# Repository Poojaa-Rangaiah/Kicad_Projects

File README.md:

# Kicad Projects
Welcome to my Kicad Projects!<br>
* This repository contains the Kicad PCB files from which I learnt to build the PCB schematic and layout from a [Udemy course](https://www.udemy.com/course/kicad-like-a-pro-3e/?couponCode=ACCAGE0923).

## 4 Layer MCU Datalogger PCB

## 2 layer MCU Datalogger PCB

## POWER SUPPLY PCB

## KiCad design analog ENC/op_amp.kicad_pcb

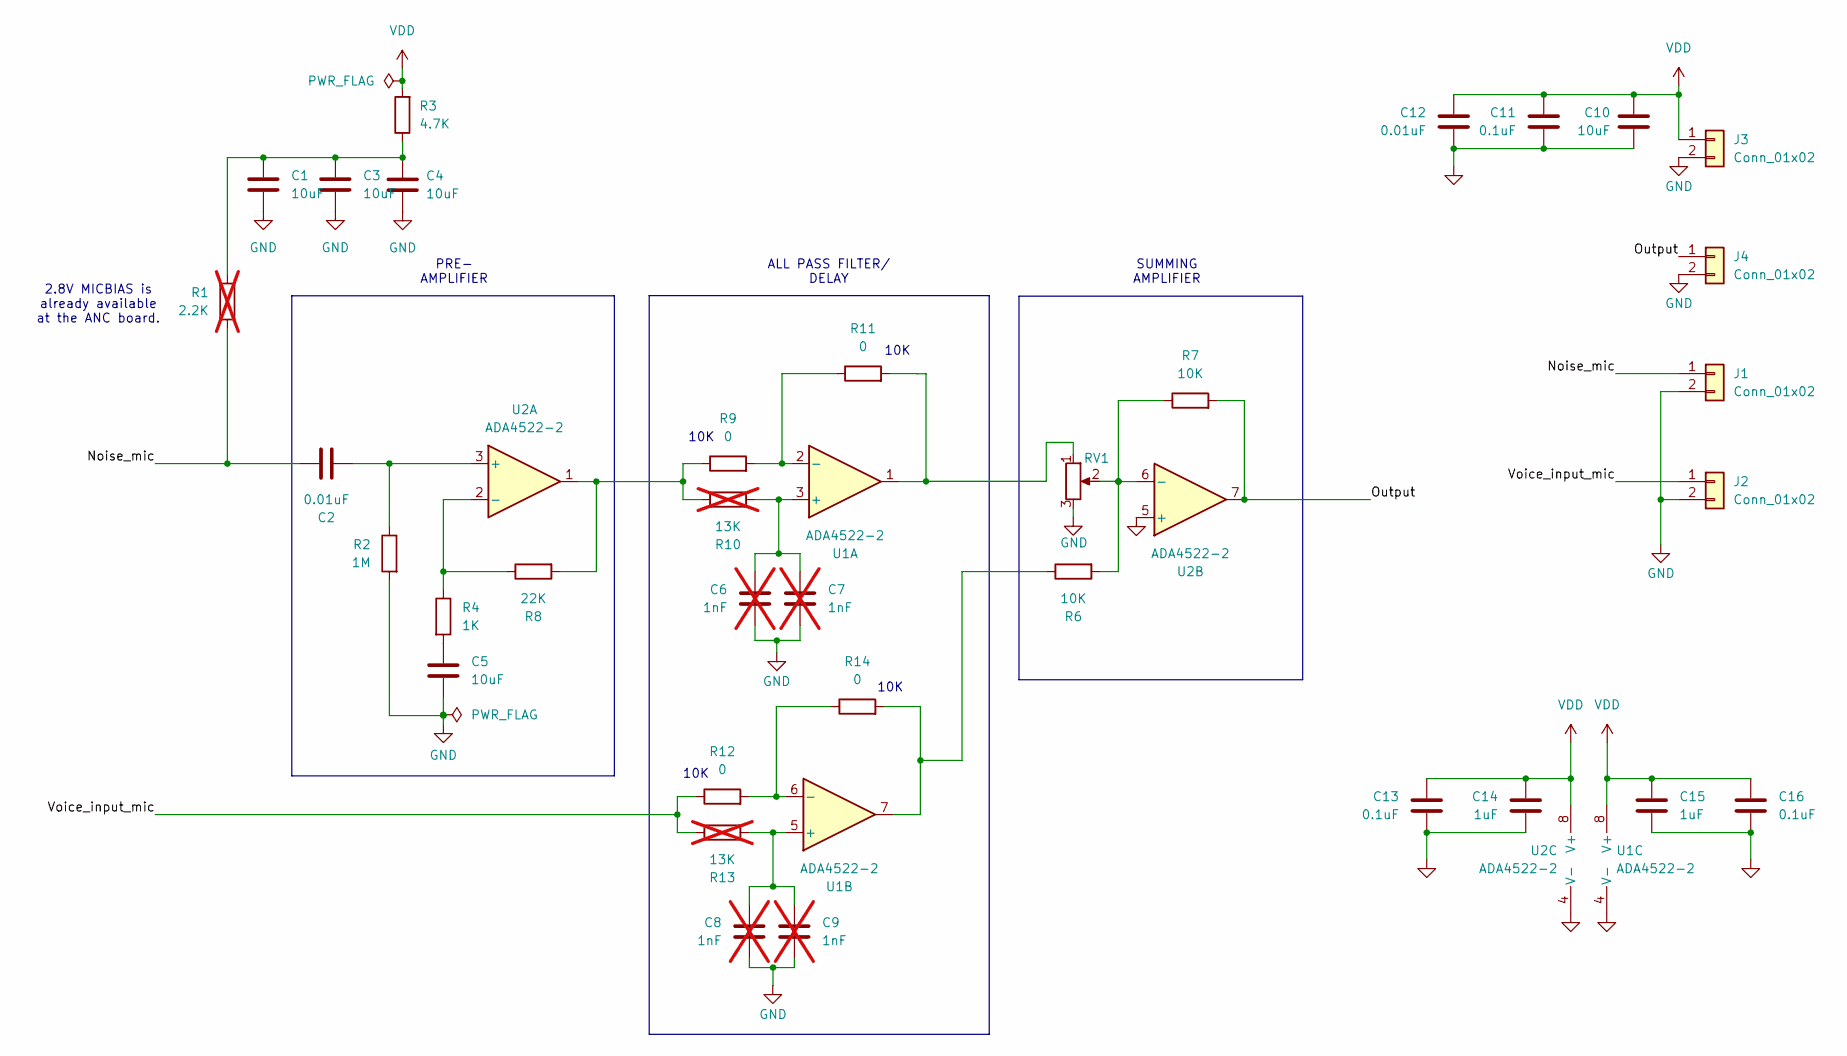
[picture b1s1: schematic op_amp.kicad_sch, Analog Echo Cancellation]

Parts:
C1, C3, C4, C5, C10: 10uF; C_0402_1005Metric_Pad0.74x0.62mm_HandSolder
C2, C12: 0.01uF; C_0402_1005Metric_Pad0.74x0.62mm_HandSolder
C6, C7, C8, C9: 1nF; C_0402_1005Metric_Pad0.74x0.62mm_HandSolder; not fitted
C11, C13, C16: 0.1uF; C_0402_1005Metric_Pad0.74x0.62mm_HandSolder
C14, C15: 1uF; C_0402_1005Metric_Pad0.74x0.62mm_HandSolder
J1, J2, J3, J4: Conn_01x02; PinHeader_2x01_P2.54mm_Vertical
R1: 2.2K; R_0402_1005Metric_Pad0.72x0.64mm_HandSolder; not fitted
R2: 1M; R_0402_1005Metric_Pad0.72x0.64mm_HandSolder
R3: 4.7K; R_0402_1005Metric_Pad0.72x0.64mm_HandSolder
R4: 1K; R_0402_1005Metric_Pad0.72x0.64mm_HandSolder
R6, R7: 10K; R_0402_1005Metric_Pad0.72x0.64mm_HandSolder
R8: 22K; R_0402_1005Metric_Pad0.72x0.64mm_HandSolder
R9, R11, R12, R14: 0; R_0402_1005Metric_Pad0.72x0.64mm_HandSolder
R10, R13: 13K; R_0402_1005Metric_Pad0.72x0.64mm_HandSolder; not fitted
RV1: R_Potentiometer; Potentiometer_Runtron_RM-065_Vertical
U1, U2: ADA4522-2; SOP65P490X110-8N

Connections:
/Noise_mic: C2.1, J1.1, R1.2
/Output: J4.1, R7.2, U2.7
/Voice_input_mic: J2.1, R12.1, R13.1
GND: C1.2, C3.2, C4.2, C5.2, C6.2, C7.2, C8.2, C9.2, C10.2, C11.2, C12.2, C13.2, C14.2, C15.2, C16.2, J1.2, J2.2, J3.2, J4.2, R2.2, RV1.3, U1.4 (V-), U2.4 (V-), U2.5 (+)
unnamed: C1.1, C3.1, C4.1, R1.1, R3.1
unnamed: C5.1, R4.2
unnamed: R8.2, R9.1, R10.1, U2.1
unnamed: R11.2, RV1.1, U1.1
unnamed: R6.1, R14.2, U1.7
unnamed: C6.1, C7.1, R10.2, U1.3 (+)
unnamed: R9.2, R11.1, U1.2 (-)
unnamed: C8.1, C9.1, R13.2, U1.5 (+)
unnamed: R12.2, R14.1, U1.6 (-)
unnamed: C2.2, R2.1, U2.3 (+)
unnamed: R4.1, R8.1, U2.2 (-)
unnamed: R6.2, R7.1, RV1.2, U2.6 (-)
VDD: C10.1, C11.1, C12.1, C13.1, C14.1, C15.1, C16.1, J3.1, R3.2, U1.8 (V+), U2.8 (V+)

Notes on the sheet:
PRE- AMPLIFIER
10K
ALL PASS FILTER/ DELAY
2.8V MICBIAS is already available at the ANC board.
SUMMING AMPLIFIER

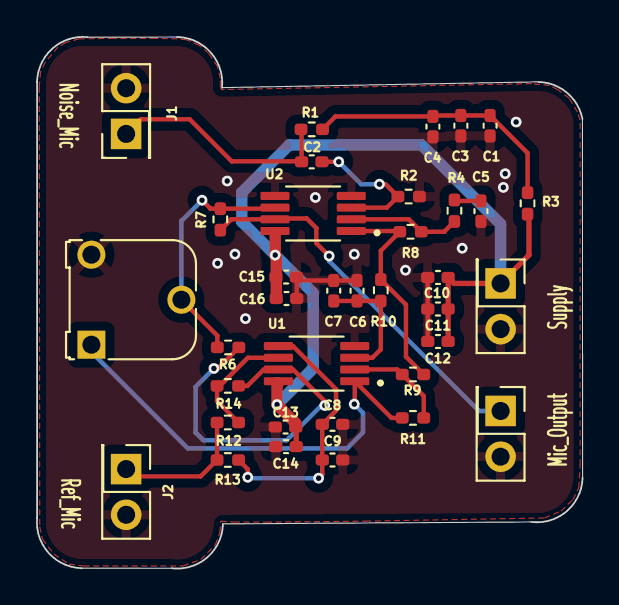
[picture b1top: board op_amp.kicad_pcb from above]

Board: 2 copper layers, 30.3 x 29.5 mm, 36 parts (0 on the bottom side), 17 nets.

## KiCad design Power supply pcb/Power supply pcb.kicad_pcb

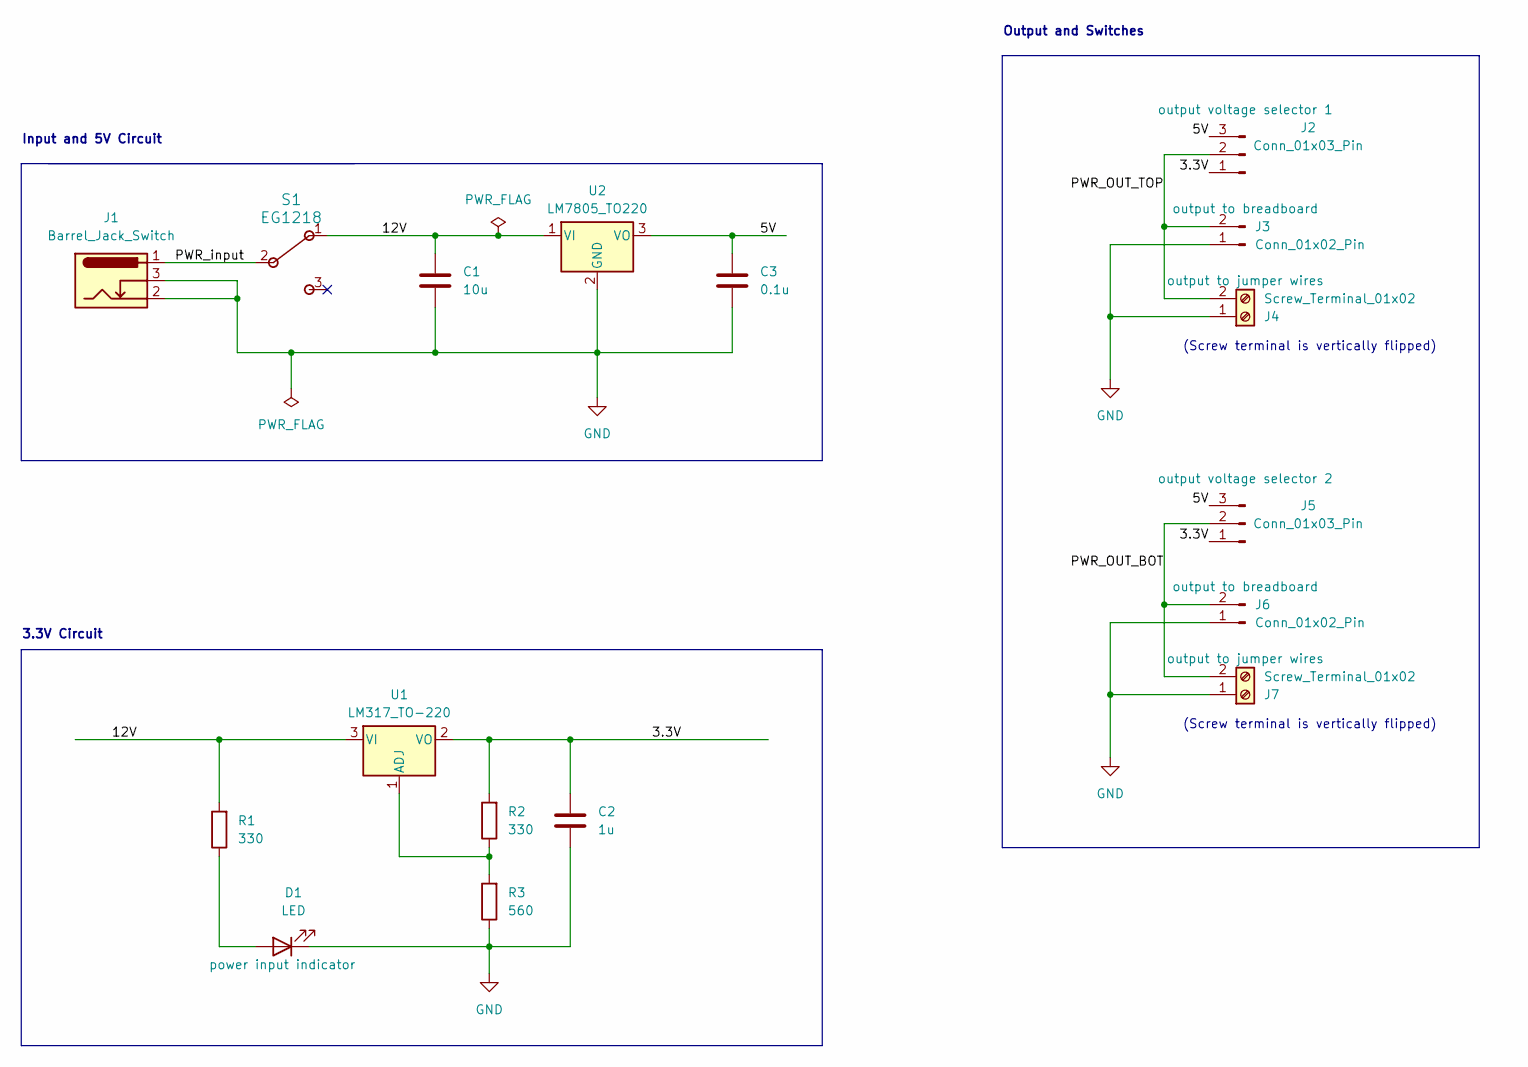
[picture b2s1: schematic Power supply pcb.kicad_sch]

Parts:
C1: 10u; C_Disc_D3.0mm_W1.6mm_P2.50mm
C2: 1u; C_Disc_D3.0mm_W1.6mm_P2.50mm
C3: 0.1u; C_Disc_D3.0mm_W1.6mm_P2.50mm
D1: LED; LED_D5.0mm
J1: Barrel_Jack_Switch; BarrelJack_Horizontal
J2, J5: Conn_01x03_Pin; PinHeader_1x03_P2.54mm_Vertical
J3, J6: Conn_01x02_Pin; PinHeader_1x02_P2.54mm_Vertical
J4, J7: Screw_Terminal_01x02; TerminalBlock_bornier-2_P5.08mm
R1, R2: 330; R_Axial_DIN0204_L3.6mm_D1.6mm_P7.62mm_Horizontal
R3: 560; R_Axial_DIN0204_L3.6mm_D1.6mm_P7.62mm_Horizontal
S1: EG1218; SW_1218_EWI
U1: LM317_TO-220; TO-220-3_Vertical
U2: LM7805_TO220; TO-220-3_Vertical

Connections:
/3.3V: C2.1, J2.1, J5.1, R2.2, U1.2 (VO)
/5V: C3.1, J2.3, J5.3, U2.3 (VO)
/12V: C1.1, R1.2, S1.1, U1.3 (VI), U2.1 (VI)
/PWR_OUT_BOT: J5.2, J6.2, J7.2
/PWR_OUT_TOP: J2.2, J3.2, J4.2
/PWR_input: J1.1, S1.2
GND: C1.2, C2.2, C3.2, D1.1 (K), J1.2, J1.3, J3.1, J4.1, J6.1, J7.1, R3.1, U2.2 (GND)
unnamed: D1.2 (A), R1.1
unnamed: R2.1, R3.2, U1.1 (ADJ)

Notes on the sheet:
3.3V Circuit
(Screw terminal is vertically flipped)
Output and Switches
Input and 5V Circuit

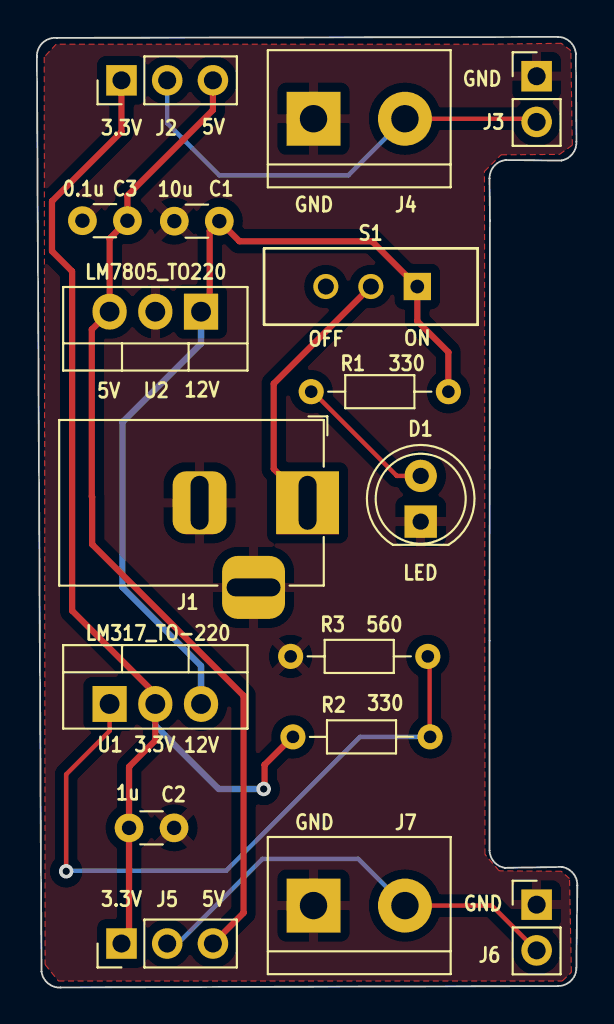
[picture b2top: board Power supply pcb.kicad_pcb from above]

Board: 2 copper layers, 30.0 x 52.8 mm, 17 parts (0 on the bottom side), 9 nets.

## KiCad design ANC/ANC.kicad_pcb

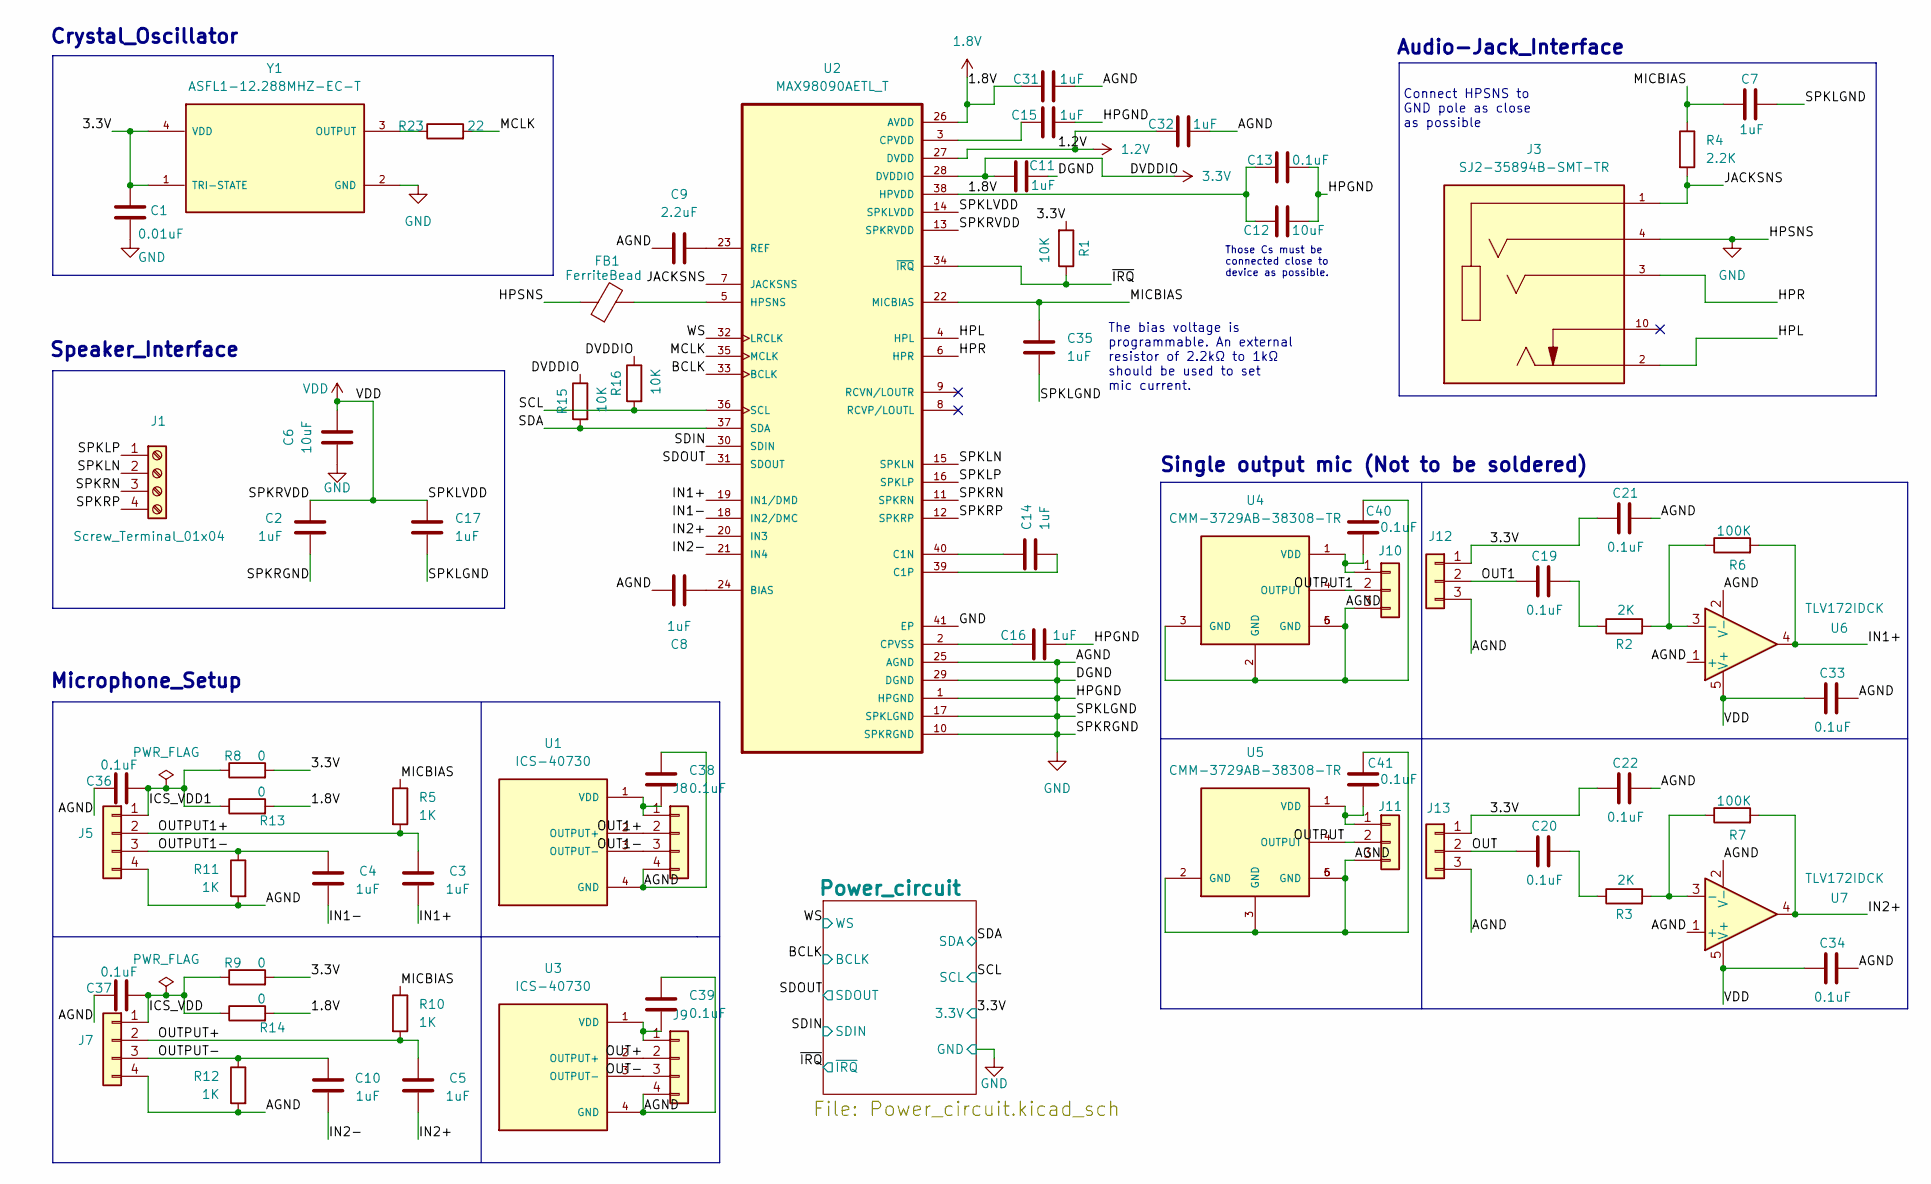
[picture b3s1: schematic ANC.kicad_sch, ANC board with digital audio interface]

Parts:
C1: 0.01uF; C_0402_1005Metric_Pad0.74x0.62mm_HandSolder
C2, C3, C4, C5, C7, C8, C10, C11, C14, C15, C16, C17, C31, C32, C35: 1uF; C_0402_1005Metric_Pad0.74x0.62mm_HandSolder
C6, C12: 10uF; C_0805_2012Metric_Pad1.18x1.45mm_HandSolder
C9: 2.2uF; C_0805_2012Metric_Pad1.18x1.45mm_HandSolder
C13, C19, C20, C21, C22, C33, C34, C36, C37, C38, C39, C40, C41: 0.1uF; C_0402_1005Metric_Pad0.74x0.62mm_HandSolder
FB1: FerriteBead; L_0402_1005Metric
J1: Screw_Terminal_01x04; TE_282836-4
J3: SJ2-35894B-SMT-TR; CUI_SJ2-35894B-SMT-TR; PARTREV 1.04
J5, J7, J8, J9: Conn_01x04; PinSocket_1x04_P2.54mm_Vertical
J10, J11, J12, J13: Conn_01x03; PinSocket_1x03_P2.54mm_Vertical
R1, R15, R16: 10K; R_0402_1005Metric_Pad0.72x0.64mm_HandSolder
R2, R3: 2K; R_0402_1005Metric_Pad0.72x0.64mm_HandSolder
R4: 2.2K; R_0402_1005Metric_Pad0.72x0.64mm_HandSolder
R5, R10, R11, R12: 1K; R_0402_1005Metric_Pad0.72x0.64mm_HandSolder
R6, R7: 100K; R_0402_1005Metric_Pad0.72x0.64mm_HandSolder
R8, R9, R13, R14: 0; R_0402_1005Metric_Pad0.72x0.64mm_HandSolder
R23: 22; R_0402_1005Metric_Pad0.72x0.64mm_HandSolder
U1, U3: ICS-40730; MIC_ICS-40730
U2: MAX98090AETL_T; QFN40P500X500X80-41N
U4, U5: CMM-3729AB-38308-TR; XDCR_CMM-3729AB-38308-TR
U6, U7: TLV172IDCK; SOT-353_SC-70-5
Y1: ASFL1-12.288MHZ-EC-T; XTAL_ASFL1-12.288MHZ-EC-T; PARTREV 04.13.11

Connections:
1.2V: C32.2, U2.27 (DVDD); also elsewhere on the board
1.8V: C12.2, C13.2, C31.2, R13.2, R14.2, U2.26 (AVDD), U2.38 (HPVDD); also elsewhere on the board
3.3V: C1.1, C11.2, C21.2, C22.2, J12.1, J13.1, R1.2, R8.2, R9.2, R15.1, R16.1, U2.28 (DVDDIO), Y1.1 (TRI-STATE), Y1.4 (VDD); also elsewhere on the board
/BCLK: U2.33 (BCLK); also elsewhere on the board
/HPL: J3.2, U2.4 (HPL)
/HPR: J3.3, U2.6 (HPR)
/ICS_VDD: C37.1, J7.1, R9.1, R14.1
/ICS_VDD1: C36.1, J5.1, R8.1, R13.1
/IN1+: C3.1, R6.2, U2.19 (IN1/DMD), U6.4
/IN1-: C4.2, U2.18 (IN2/DMC)
/IN2+: C5.1, R7.2, U2.20 (IN3), U7.4
/IN2-: C10.2, U2.21 (IN4)
/JACKSNS: J3.1, R4.2, U2.7 (JACKSNS)
/MCLK: R23.2, U2.35 (MCLK)
/MICBIAS: C7.1, C35.1, R4.1, R5.1, R10.1, U2.22 (MICBIAS)
/OUT: C20.2, J13.2
/OUT1: C19.2, J12.2
/OUT1+: J8.2, U1.2 (OUTPUT+)
/OUT1-: J8.3, U1.3 (OUTPUT-)
/OUT+: J9.2, U3.2 (OUTPUT+)
/OUT-: J9.3, U3.3 (OUTPUT-)
/OUTPUT: J11.2, U5.4 (OUTPUT)
/OUTPUT1: J10.2, U4.4 (OUTPUT)
/OUTPUT1+: C3.2, J5.2, R5.2
/OUTPUT1-: C4.1, J5.3, R11.1
/OUTPUT+: C5.2, J7.2, R10.2
/OUTPUT-: C10.1, J7.3, R12.1
/SCL: R16.2, U2.36 (SCL); also elsewhere on the board
/SDA: R15.2, U2.37 (SDA); also elsewhere on the board
/SDIN: U2.30 (SDIN); also elsewhere on the board
/SDOUT: U2.31 (SDOUT); also elsewhere on the board
/SPKLN: J1.2, U2.15 (SPKLN)
/SPKLP: J1.1, U2.16 (SPKLP)
/SPKRN: J1.3, U2.11 (SPKRN)
/SPKRP: J1.4, U2.12 (SPKRP)
/WS: U2.32 (LRCLK); also elsewhere on the board
/~IRQ: R1.1, U2.34 (~IRQ); also elsewhere on the board
GND: C1.2, C2.2, C6.1, C7.2, C8.2, C9.2, C11.1, C12.1, C13.1, C15.1, C16.1, C17.2, C21.1, C22.1, C31.1, C32.1, C33.1, C34.1, C35.2, C36.2, C37.2, C38.1, C39.1, C40.1, C41.1, FB1.1, J3.4, J5.4, J7.4, J8.4, J9.4, J10.3, J11.3, J12.3, J13.3, R11.2, R12.2, U1.4 (GND), U2.1 (HPGND), U2.10 (SPKRGND), U2.17 (SPKLGND), U2.25 (AGND), U2.29 (DGND), U2.41 (EP), U3.4 (GND), U4.2 (GND), U4.3 (GND), U4.5 (GND), U4.6 (GND), U5.2 (GND), U5.3 (GND), U5.5 (GND), U5.6 (GND), U6.1 (+), U6.2 (V-), U7.1 (+), U7.2 (V-), Y1.2 (GND); also elsewhere on the board
unnamed: C19.1, R2.1
unnamed: C20.1, R3.1
unnamed: C38.2, J8.1, U1.1 (VDD)
unnamed: C39.2, J9.1, U3.1 (VDD)
unnamed: C40.2, J10.1, U4.1 (VDD)
unnamed: C41.2, J11.1, U5.1 (VDD)
unnamed: C8.1, U2.24 (BIAS)
unnamed: C14.2, U2.40 (C1N)
unnamed: C14.1, U2.39 (C1P)
unnamed: C15.2, U2.3 (CPVDD)
unnamed: C16.2, U2.2 (CPVSS)
unnamed: FB1.2, U2.5 (HPSNS)
unnamed: C9.1, U2.23 (REF)
unnamed: R2.2, R6.1, U6.3 (-)
unnamed: R3.2, R7.1, U7.3 (-)
unnamed: R23.1, Y1.3 (OUTPUT)
VDD: C2.1, C6.2, C17.1, C33.2, C34.2, U2.13 (SPKRVDD), U2.14 (SPKLVDD), U6.5 (V+), U7.5 (V+); also elsewhere on the board

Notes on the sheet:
Microphone_Setup
Single output mic (Not to be soldered)
The bias voltage is programmable. An external resistor of 2.2kΩ to 1kΩ should be used to set mic current.
Connect HPSNS to GND pole as close as possible
Those Cs must be connected close to device as possible.
Audio-Jack_Interface
Crystal_Oscillator
Speaker_Interface

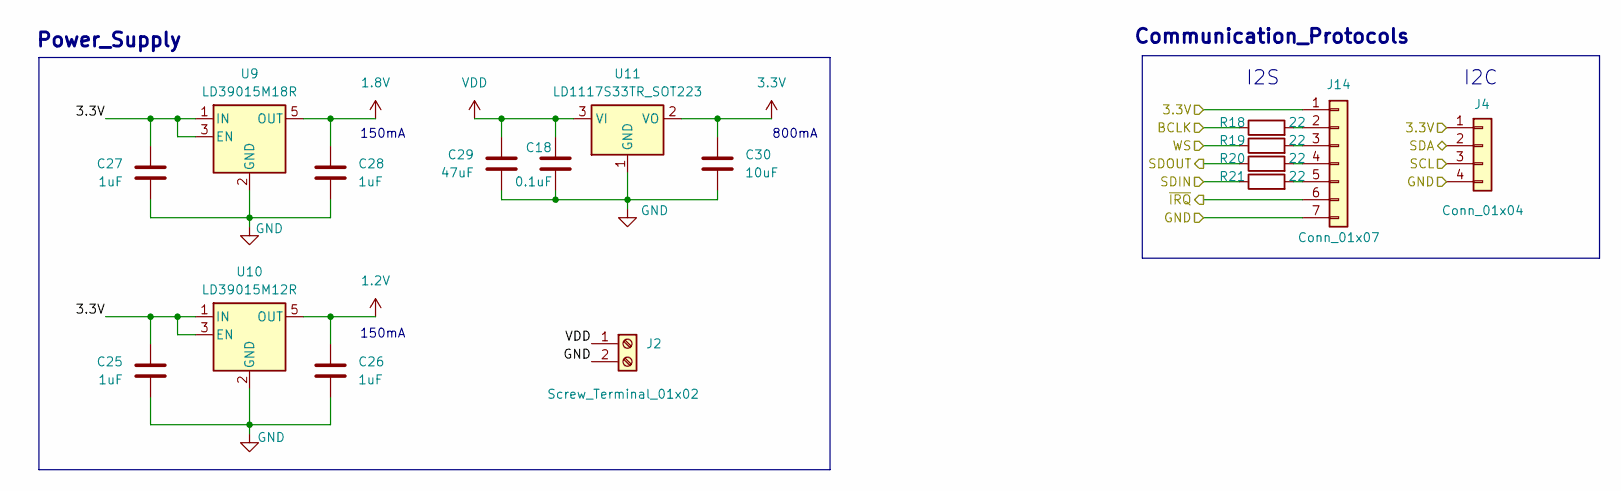
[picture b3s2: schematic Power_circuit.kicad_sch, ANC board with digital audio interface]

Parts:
C18: 0.1uF; C_0402_1005Metric_Pad0.74x0.62mm_HandSolder
C25, C26, C27, C28: 1uF; C_0402_1005Metric_Pad0.74x0.62mm_HandSolder
C29: 47uF; C_0805_2012Metric_Pad1.18x1.45mm_HandSolder
C30: 10uF; C_0805_2012Metric_Pad1.18x1.45mm_HandSolder
J2: Screw_Terminal_01x02; TE_282836-2
J4: Conn_01x04; PinHeader_1x04_P2.54mm_Vertical
J14: Conn_01x07; PinHeader_1x07_P2.54mm_Vertical
R18, R19, R20, R21: 22; R_0402_1005Metric_Pad0.72x0.64mm_HandSolder
U9: LD39015M18R; SOT-23-5
U10: LD39015M12R; SOT-23-5
U11: LD1117S33TR_SOT223; SOT-223-3_TabPin2

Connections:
1.2V: C26.1, U10.5 (OUT); also elsewhere on the board
1.8V: C28.1, U9.5 (OUT); also elsewhere on the board
3.3V: C25.1, C27.1, C30.1, J4.1, J14.1, U9.1 (IN), U9.3 (EN), U10.1 (IN), U10.3 (EN), U11.2 (VO); also elsewhere on the board
/BCLK: R18.1; also elsewhere on the board
/SCL: J4.3; also elsewhere on the board
/SDA: J4.2; also elsewhere on the board
/SDIN: R21.1; also elsewhere on the board
/SDOUT: R20.1; also elsewhere on the board
/WS: R19.1; also elsewhere on the board
/~IRQ: J14.6; also elsewhere on the board
GND: C18.1, C25.2, C26.2, C27.2, C28.2, C29.2, C30.2, J2.2, J4.4, J14.7, U9.2 (GND), U10.2 (GND), U11.1 (GND); also elsewhere on the board
unnamed: J14.2, R18.2
unnamed: J14.3, R19.2
unnamed: J14.4, R20.2
unnamed: J14.5, R21.2
VDD: C18.2, C29.1, J2.1, U11.3 (VI); also elsewhere on the board

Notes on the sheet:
150mA
Communication_Protocols
I2S
I2C
800mA
Power_Supply

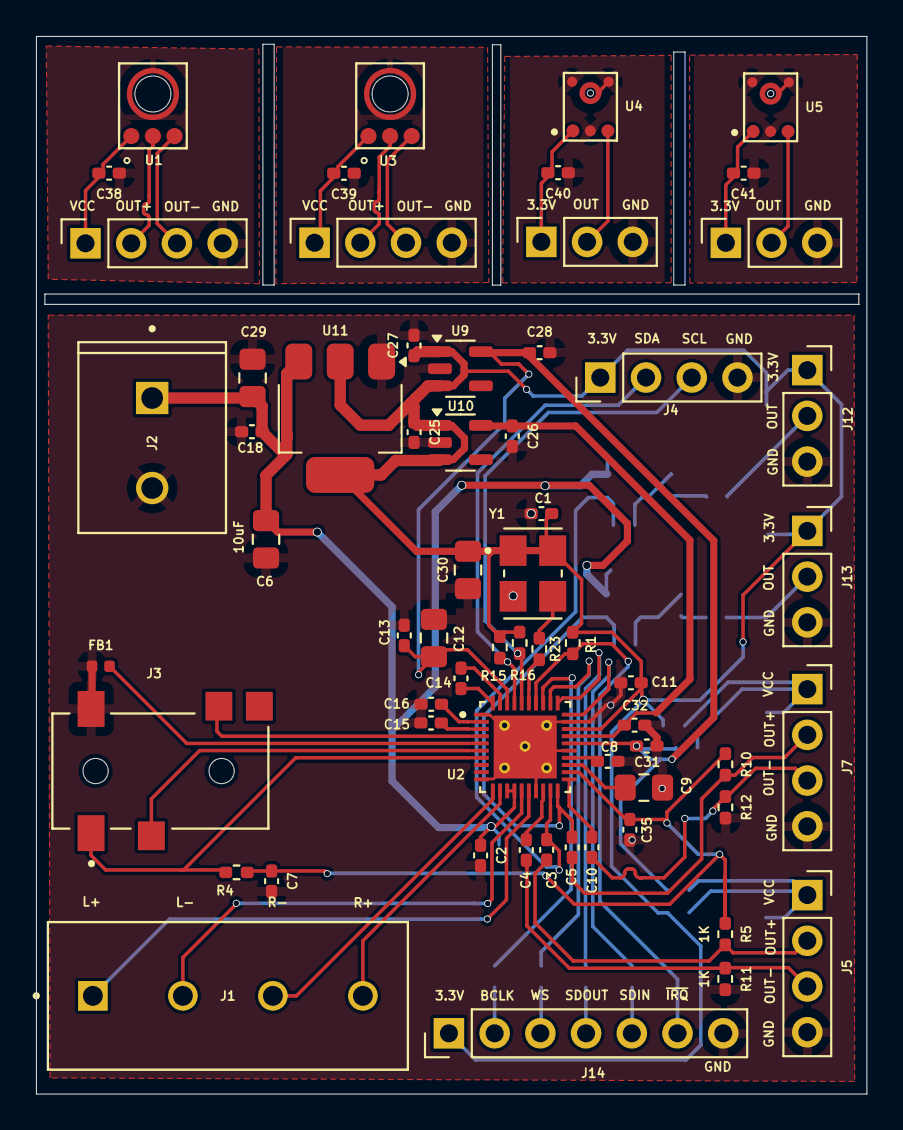
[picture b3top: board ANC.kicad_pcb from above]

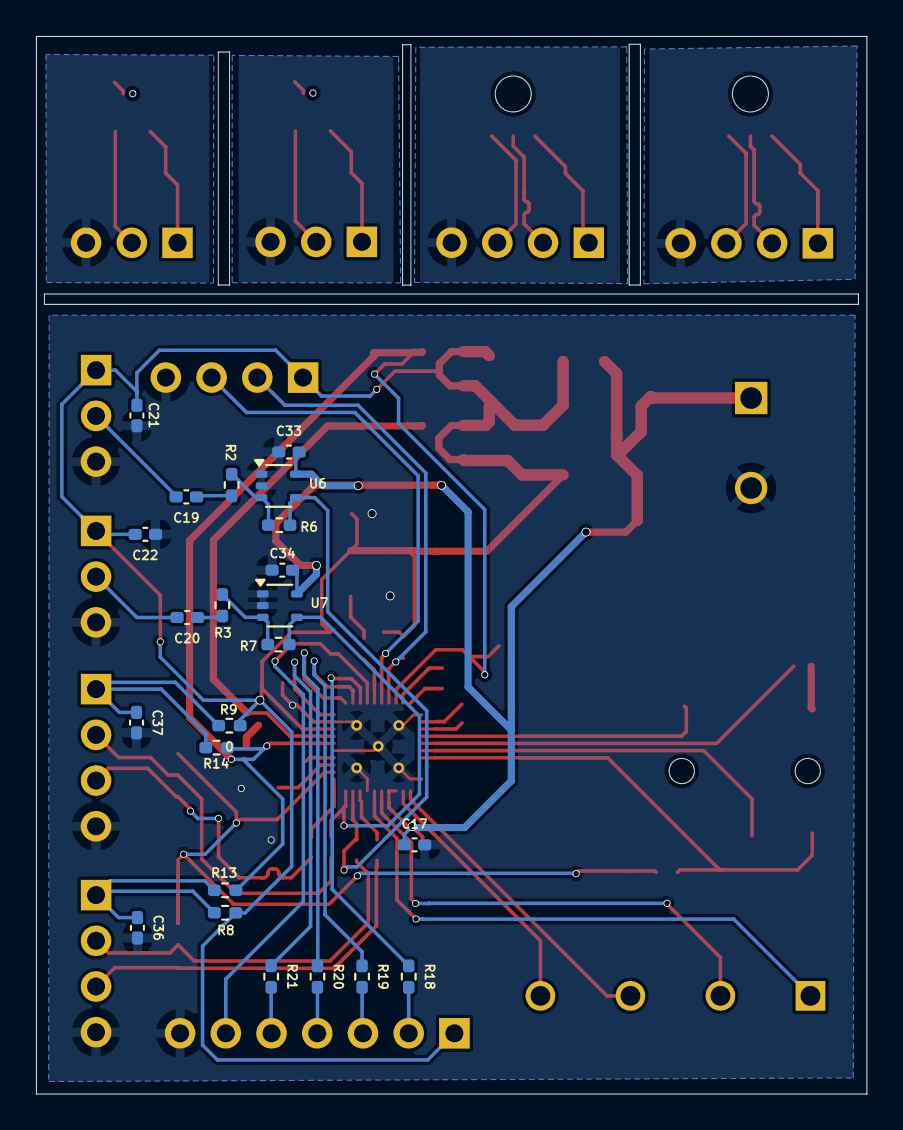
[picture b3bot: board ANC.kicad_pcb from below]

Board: 2 copper layers, 46.1 x 58.8 mm, 85 parts (23 on the bottom side), 59 nets.

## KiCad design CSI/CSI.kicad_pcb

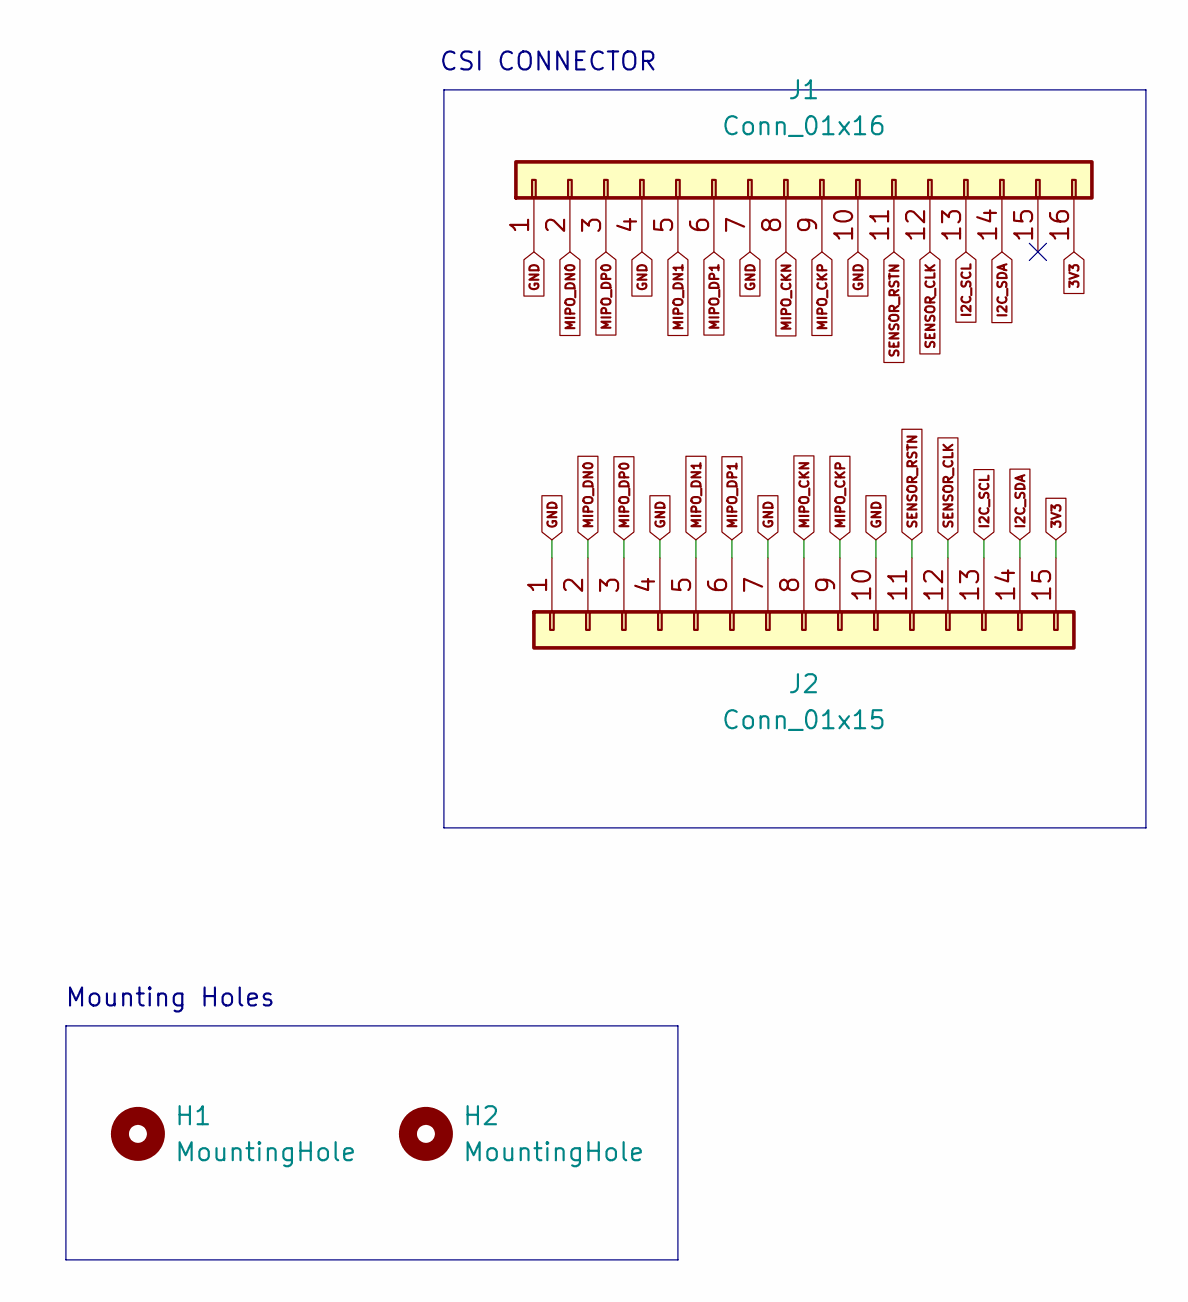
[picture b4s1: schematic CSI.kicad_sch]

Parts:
H1, H2: MountingHole; MountingHole_2.1mm
J1: Conn_01x16; CON_527461671_MOL
J2: Conn_01x15; TE_1-84952-5_1x15-1MP_P1.0mm_Horizontal

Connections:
3V3: J1.16, J2.15
GND: J1.1, J1.4, J1.7, J1.10, J2.1, J2.4, J2.7, J2.10
I2C_SCL: J1.13, J2.13
I2C_SDA: J1.14, J2.14
MIPO_CKN: J1.8, J2.8
MIPO_CKP: J1.9, J2.9
MIPO_DN0: J1.2, J2.2
MIPO_DN1: J1.5, J2.5
MIPO_DP0: J1.3, J2.3
MIPO_DP1: J1.6, J2.6
SENSOR_CLK: J1.12, J2.12
SENSOR_RSTN: J1.11, J2.11

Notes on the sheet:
Mounting Holes
CSI CONNECTOR

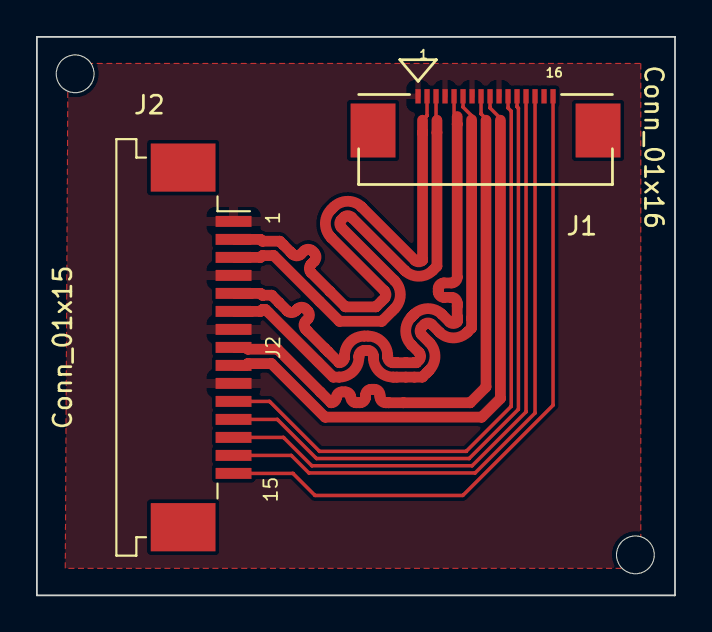
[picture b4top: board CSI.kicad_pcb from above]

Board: 2 copper layers, 35.5 x 31.0 mm, 4 parts (0 on the bottom side), 12 nets.

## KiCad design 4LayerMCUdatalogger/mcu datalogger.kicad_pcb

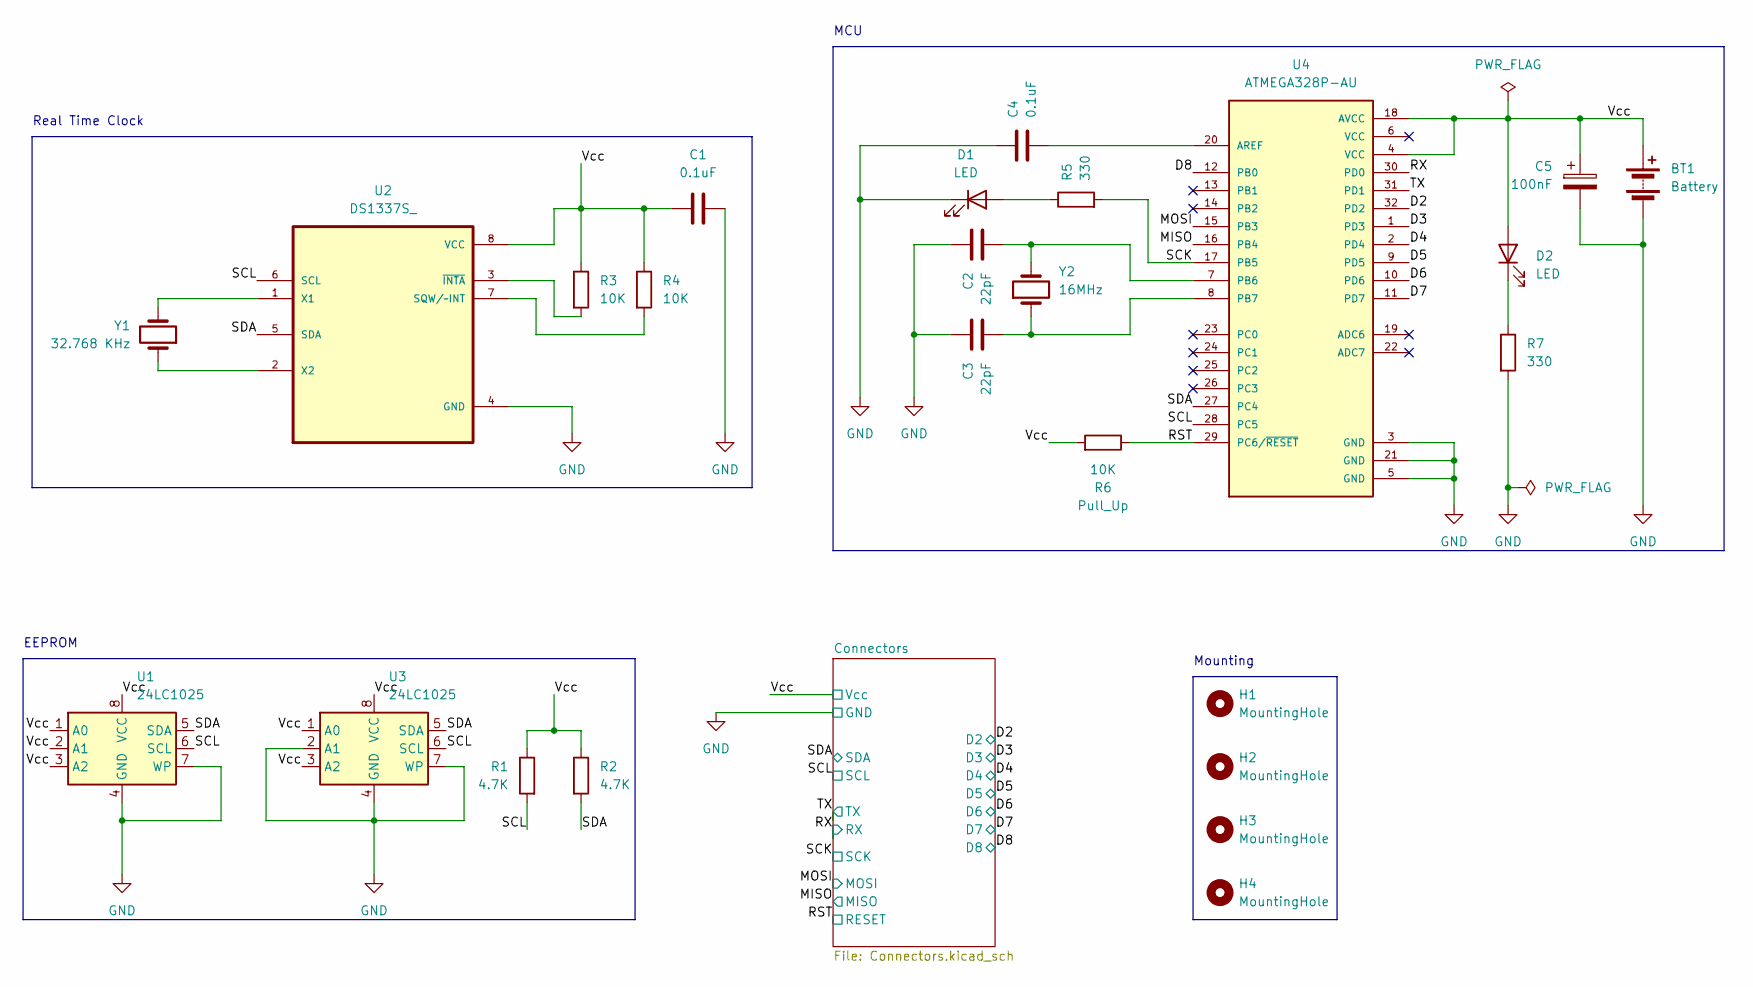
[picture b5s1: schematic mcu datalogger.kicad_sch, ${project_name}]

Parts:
BT1: Battery; PinHeader_1x02_P2.54mm_Vertical
C1, C4: 0.1uF; C_0805_2012Metric
C2, C3: 22pF; C_0805_2012Metric
C5: 100nF; C_0805_2012Metric
D1, D2: LED; LED_0805_2012Metric
H1, H2, H3, H4: MountingHole; MountingHole_2.1mm
R1, R2: 4.7K; R_0805_2012Metric
R3, R4, R6: 10K; R_0805_2012Metric
R5, R7: 330; R_0805_2012Metric
U1, U3: 24LC1025; SOIC-8_3.9x4.9mm_P1.27mm
U2: DS1337S_; SOIC127P600X175-8N
U4: ATMEGA328P-AU; QFP80P900X900X120-32N; PARTREV 8271A
Y1: 32.768 KHz; Crystal_SMD_5032-2Pin_5.0x3.2mm_HandSoldering
Y2: 16MHz; Crystal_SMD_5032-2Pin_5.0x3.2mm_HandSoldering

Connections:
/D2: U4.32 (PD2); also elsewhere on the board
/D3: U4.1 (PD3); also elsewhere on the board
/D4: U4.2 (PD4); also elsewhere on the board
/D5: U4.9 (PD5); also elsewhere on the board
/D6: U4.10 (PD6); also elsewhere on the board
/D7: U4.11 (PD7); also elsewhere on the board
/D8: U4.12 (PB0); also elsewhere on the board
/MISO: U4.16 (PB4); also elsewhere on the board
/MOSI: U4.15 (PB3); also elsewhere on the board
/RST: R6.1, U4.29 (PC6/~RESET); also elsewhere on the board
/RX: U4.30 (PD0); also elsewhere on the board
/SCK: R5.2, U4.17 (PB5); also elsewhere on the board
/SCL: R1.2, U1.6 (SCL), U2.6 (SCL), U3.6 (SCL), U4.28 (PC5); also elsewhere on the board
/SDA: R2.2, U1.5 (SDA), U2.5 (SDA), U3.5 (SDA), U4.27 (PC4); also elsewhere on the board
/TX: U4.31 (PD1); also elsewhere on the board
/Vcc: BT1.1 (+), C1.1, C5.1, D2.2 (A), R1.1, R2.1, R3.1, R4.1, R6.2, U1.1 (A0), U1.2 (A1), U1.3 (A2), U1.8 (VCC), U2.8 (VCC), U3.1 (A0), U3.3 (A2), U3.8 (VCC), U4.4 (VCC), U4.18 (AVCC); also elsewhere on the board
GND: BT1.2 (-), C1.2, C2.1, C3.1, C4.1, C5.2, D1.1 (K), R7.2, U1.4 (GND), U1.7 (WP), U2.4 (GND), U3.2 (A1), U3.4 (GND), U3.7 (WP), U4.3 (GND), U4.5 (GND), U4.21 (GND); also elsewhere on the board
unnamed: D1.2 (A), R5.1
unnamed: D2.1 (K), R7.1
unnamed: R4.2, U2.7 (SQW/~INT)
unnamed: U2.1 (X1), Y1.2
unnamed: U2.2 (X2), Y1.1
unnamed: R3.2, U2.3 (~INTA)
unnamed: C4.2, U4.20 (AREF)
unnamed: C2.2, U4.7 (PB6), Y2.2
unnamed: C3.2, U4.8 (PB7), Y2.1

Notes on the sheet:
Real Time Clock
MCU
EEPROM
Mounting

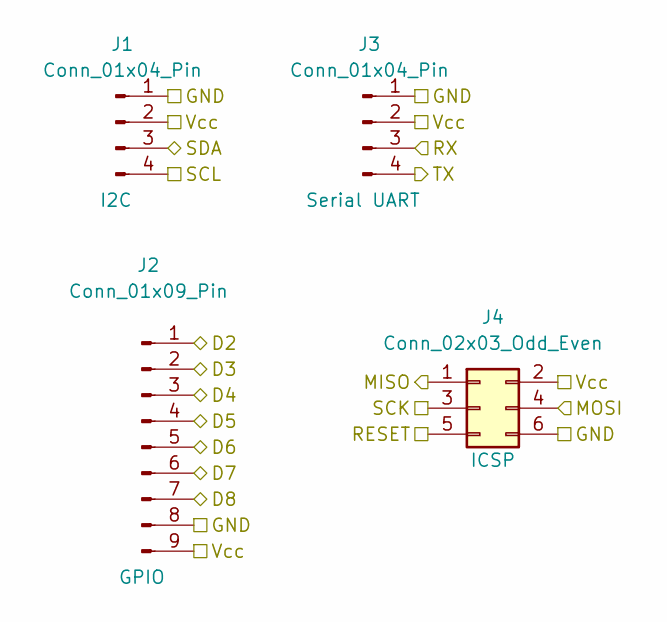
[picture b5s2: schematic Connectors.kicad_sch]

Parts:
J1, J3: Conn_01x04_Pin; PinHeader_1x04_P2.54mm_Vertical
J2: Conn_01x09_Pin; PinHeader_1x09_P2.54mm_Vertical
J4: Conn_02x03_Odd_Even; PinHeader_2x03_P2.54mm_Vertical

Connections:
/D2: J2.1; also elsewhere on the board
/D3: J2.2; also elsewhere on the board
/D4: J2.3; also elsewhere on the board
/D5: J2.4; also elsewhere on the board
/D6: J2.5; also elsewhere on the board
/D7: J2.6; also elsewhere on the board
/D8: J2.7; also elsewhere on the board
/MISO: J4.1; also elsewhere on the board
/MOSI: J4.4; also elsewhere on the board
/RST: J4.5; also elsewhere on the board
/RX: J3.3; also elsewhere on the board
/SCK: J4.3; also elsewhere on the board
/SCL: J1.4; also elsewhere on the board
/SDA: J1.3; also elsewhere on the board
/TX: J3.4; also elsewhere on the board
/Vcc: J1.2, J2.9, J3.2, J4.2; also elsewhere on the board
GND: J1.1, J2.8, J3.1, J4.6; also elsewhere on the board

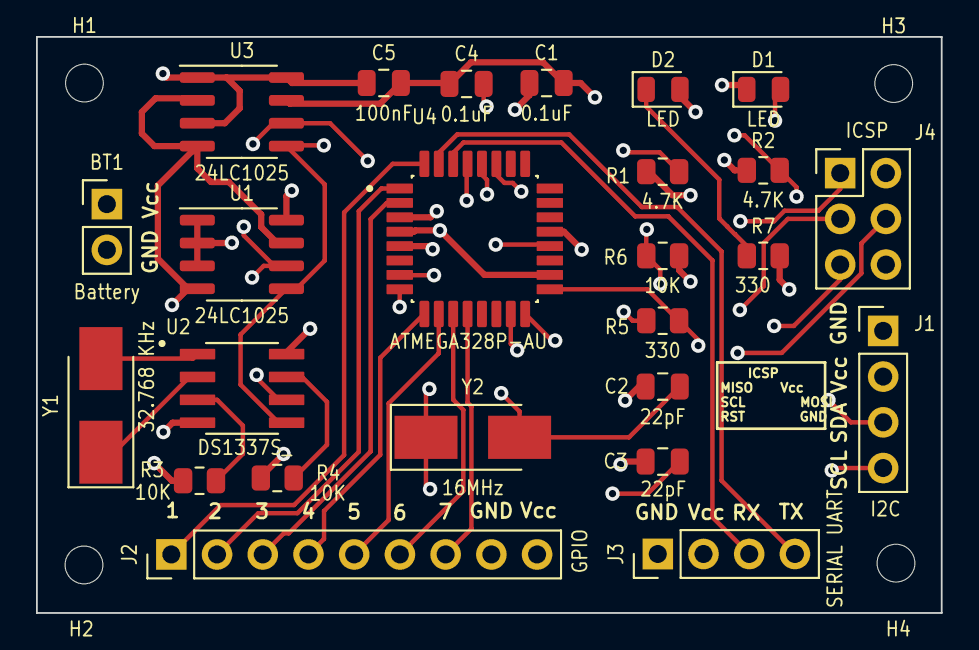
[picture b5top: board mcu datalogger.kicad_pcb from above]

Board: 4 copper layers, 50.3 x 32.0 mm, 29 parts (0 on the bottom side), 26 nets.

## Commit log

2023-12-14 New testing file for Kicad
2023-12-14 added gitignore file and pushed into the remote repository
2023-12-14 Create README.md
    Added README.md in master branch
2023-12-14 Setup of EEschema for new project.
2023-12-14 Added required symbols to the schematic sheets.
2023-12-14 Added 2 more resitors and assembled the symbols accordingly.
2023-12-14 Added values to the components.
2023-12-14 Completed the footprints association.
2023-12-15 Completed the wiring & labeling of the main sheet
2023-12-16 Completed wiring in the second sheet.
2023-12-16 Allocated Power and Default Net classes.
2023-12-16 Completed Comments.
2023-12-16 Setup PCBnew.
2024-01-01 Completed the footprints placement.
2024-01-02 Done routing the tracks.
2024-01-06 Completed routing and copper filling.
2024-01-06 Fixed outstanding issues.
2024-01-17 Fixed 2 bugs in the schematic.
2024-01-25 Completed 2 layer PCB project.
2024-01-25 Completed 2 layer PCB.
2024-02-11 Modified.
2024-02-15 Deleted files.
2024-03-09 Completed 2layer MCU Datalogger PCB.
2024-03-09 Completed 4layer PCB routing.
2024-03-09 Small modifications.
2024-03-10 Added Board Characteristics.
2024-03-10 Successfully completed the 4Layer MCU Datalogger PCB project.
2024-04-06 Updated.
2024-04-09 Recovered 2stack PCB from Git merge conflicts but not 4stack!
2024-04-09 Recovered 4stack PCBnew.
2024-04-15 Completed the recovered file.
2024-06-26 Uploaded.
2024-07-09 added.
2024-07-09 Updated...
2024-08-04 Updated ANC.
2024-08-13 Added ANC
2024-08-15 Optimized.
2025-02-04 Uploaded the ENC PCB.
